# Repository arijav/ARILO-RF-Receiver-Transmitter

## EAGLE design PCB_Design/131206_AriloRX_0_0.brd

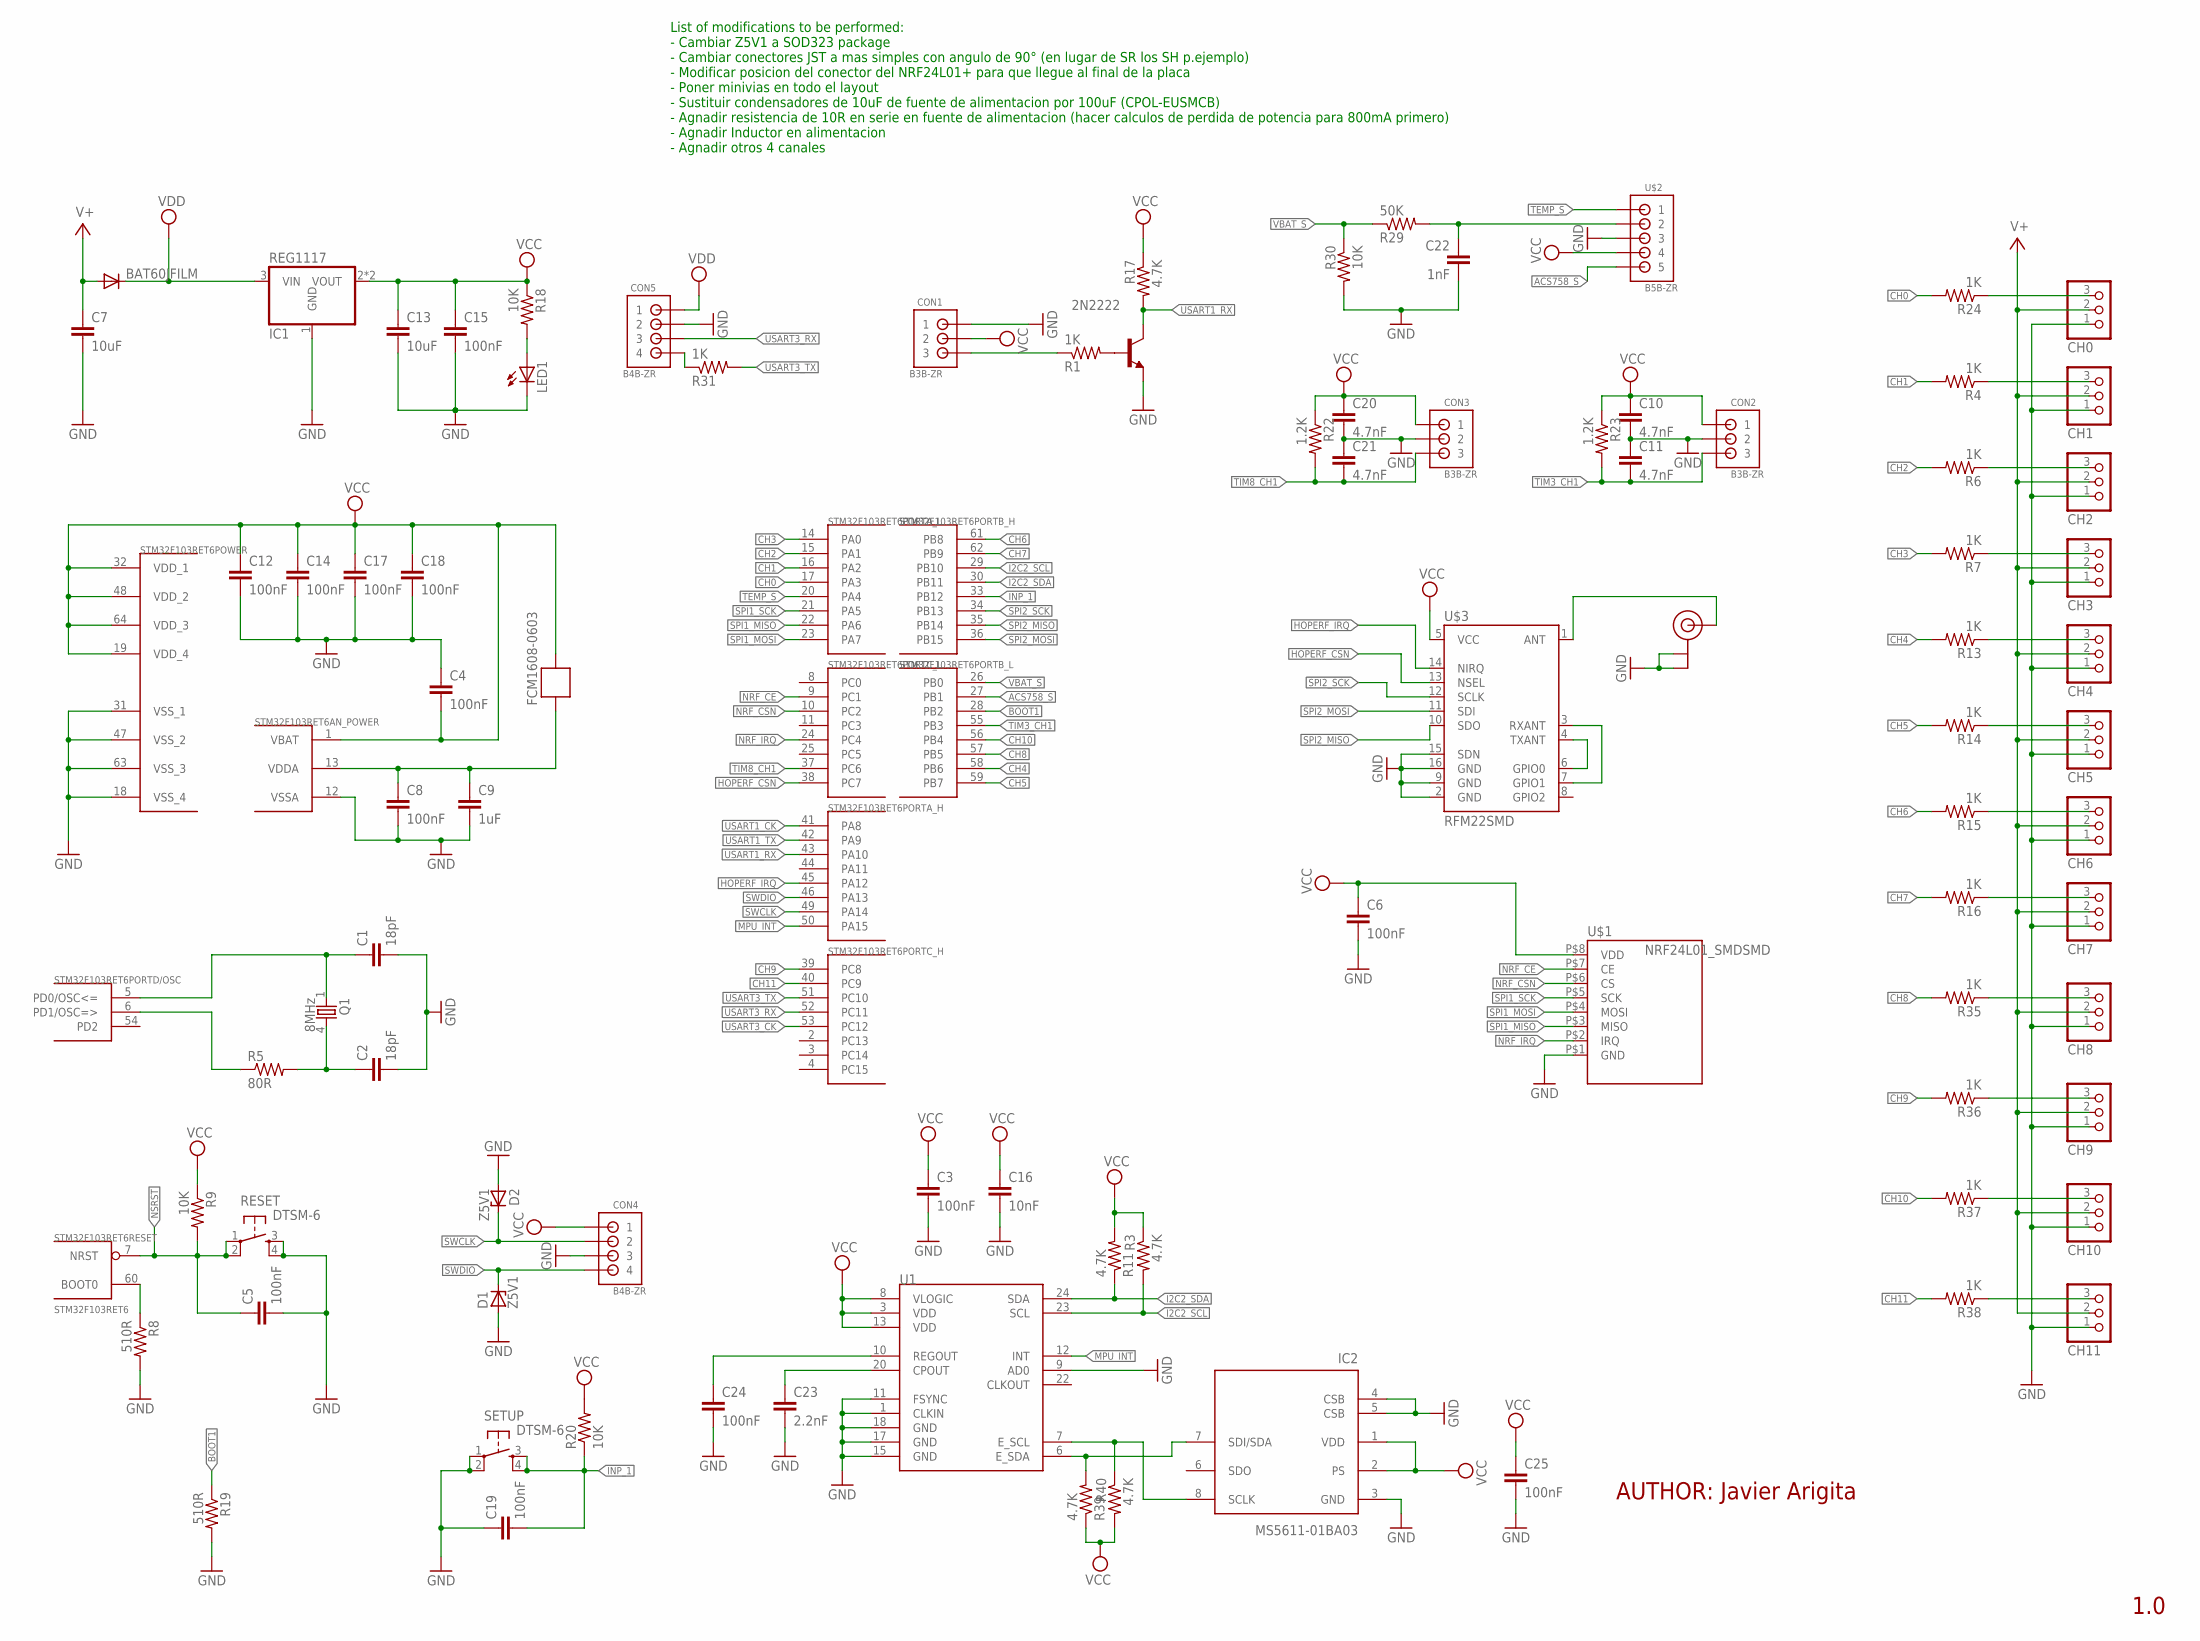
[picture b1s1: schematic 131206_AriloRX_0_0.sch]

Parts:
2N2222: MMBT2222ALT1-NPN-SOT23-BEC; SOT23-BEC
BAT60JFILM: DIODE-SOD323-R; SOD323-R
C1, C2: 18pF; C0805
C3, C4, C5, C6, C8, C12, C14, C15, C17, C18, C19, C24, C25: 100nF; C0805
C7, C13: 10uF; C3216
C9: 1uF; C3216
C10, C11, C20, C21: 4.7nF; C0805
C16: 10nF; C0805
C22: 1nF; C0805
C23: 2.2nF; C0805
CH0, CH1, CH2, CH3, CH4, CH5, CH6, CH7, CH8, CH9, CH10, CH11: PINHD-1X3; 1X03
CON1, CON2, CON3: B3B-ZR
CON4, CON5: B4B-ZR
D1, D2: Z5V1; SOD80C
FCM1608-0603: FERRITE-BEAD; R0603
IC1: REG1117; SOT223
IC2: MS5611-01BA03; SON125P300X500X100-8N
LED1: LED0805; CHIPLED_0805
Q1: 8MHz; MA506
R1, R4, R6, R7, R13, R14, R15, R16, R24, R31, R35, R36, R37, R38: 1K; R0805
R3, R11, R17, R39, R40: 4.7K; R0805
R5: 80R; R0805
R8, R19: 510R; R0805
R9, R18, R20, R30: 10K; R0805
R22, R23: 1.2K; R0805
R29: 50K; R0805
RESET: DTSM-6
SETUP: DTSM-6
STM32F103RET6: STM32F103RET6; TQFP64
U1: MPU-9150QFN-24-NP; QFN-24-NP
U$1: NRF24L01_SMDSMD; NRF24L01_SMD
U$2: B5B-ZR
U$3: RFM22SMD; RFM22-XXX-S2
U$4: U.FL

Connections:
ACS758_S: STM32F103RET6.27 (PB1), U$2.5
BOOT1: R19.1, STM32F103RET6.28 (PB2)
CH0: R24.2, STM32F103RET6.17 (PA3)
CH1: R4.2, STM32F103RET6.16 (PA2)
CH2: R6.2, STM32F103RET6.15 (PA1)
CH3: R7.2, STM32F103RET6.14 (PA0)
CH4: R13.2, STM32F103RET6.58 (PB6)
CH5: R14.2, STM32F103RET6.59 (PB7)
CH6: R15.2, STM32F103RET6.61 (PB8)
CH7: R16.2, STM32F103RET6.62 (PB9)
CH8: R35.2, STM32F103RET6.57 (PB5)
CH9: R36.2, STM32F103RET6.39 (PC8)
CH10: R37.2, STM32F103RET6.56 (PB4)
CH11: R38.2, STM32F103RET6.40 (PC9)
GND: 2N2222.E, C1.2, C2.2, C3.2, C4.1, C5.2, C6.2, C7.2, C8.2, C9.2, C10.2, C11.1, C12.2, C13.2, C14.2, C15.2, C16.2, C17.2, C18.2, C19.1, C20.2, C21.1, C22.2, C23.2, C24.2, C25.2, CH0.1, CH1.1, CH2.1, CH3.1, CH4.1, CH5.1, CH6.1, CH7.1, CH8.1, CH9.1, CH10.1, CH11.1, CON1.1, CON2.2, CON3.2, CON4.3, CON5.2, D1.A, D2.A, IC1.1 (GND), IC2.3 (GND), IC2.4 (CSB), IC2.5 (CSB), LED1.C, R8.2, R19.2, R30.2, RESET.3, RESET.4, SETUP.1, SETUP.2, STM32F103RET6.12 (VSSA), STM32F103RET6.18 (VSS_4), STM32F103RET6.31 (VSS_1), STM32F103RET6.47 (VSS_2), STM32F103RET6.63 (VSS_3), U1.1 (CLKIN), U1.9 (AD0), U1.11 (FSYNC), U1.15 (GND), U1.17 (GND), U1.18 (GND), U$1.P$1 (GND), U$2.3, U$3.2 (GND), U$3.9 (GND), U$3.15 (SDN), U$3.16 (GND), U$4.P$1 (GND), U$4.P$2 (GND)
HOPERF_CSN: STM32F103RET6.38 (PC7), U$3.13 (NSEL)
HOPERF_IRQ: STM32F103RET6.45 (PA12), U$3.14 (NIRQ)
I2C2_SCL: R3.2, STM32F103RET6.29 (PB10), U1.23 (SCL)
I2C2_SDA: R11.1, STM32F103RET6.30 (PB11), U1.24 (SDA)
INP_1: C19.2, R20.1, SETUP.3, SETUP.4, STM32F103RET6.33 (PB12)
MPU_INT: STM32F103RET6.50 (PA15), U1.12 (INT)
unnamed: C1.1, Q1.1, STM32F103RET6.5 (PD0/OSC<=)
unnamed: R5.1, STM32F103RET6.6 (PD1/OSC=>)
unnamed: C2.1, Q1.4 (2), R5.2
unnamed: R8.1, STM32F103RET6.60 (BOOT0)
unnamed: U$3.3 (RXANT), U$3.7 (GPIO1)
unnamed: U$3.4 (TXANT), U$3.6 (GPIO0)
unnamed: U$3.1 (ANT), U$4.P$3 (SIGNAL)
unnamed: CH0.3, R24.1
unnamed: LED1.A, R18.2
unnamed: CON5.4, R31.1
unnamed: CH8.3, R35.1
unnamed: CON1.3, R1.1
unnamed: C22.1, R29.2, U$2.2
unnamed: 2N2222.B, R1.2
unnamed: C8.1, C9.1, FCM1608-0603.2, STM32F103RET6.13 (VDDA)
unnamed: CH2.3, R6.1
unnamed: CH4.3, R13.1
unnamed: CH9.3, R36.1
unnamed: CH10.3, R37.1
unnamed: CH11.3, R38.1
unnamed: IC2.8 (SCLK), R40.1, U1.7 (E_SCL)
unnamed: IC2.7 (SDI/SDA), R39.2, U1.6 (E_SDA)
unnamed: CH3.3, R7.1
unnamed: CH6.3, R15.1
unnamed: C23.1, U1.20 (CPOUT)
unnamed: CH5.3, R14.1
unnamed: CH7.3, R16.1
unnamed: C24.1, U1.10 (REGOUT)
unnamed: CH1.3, R4.1
NRF_CE: STM32F103RET6.9 (PC1), U$1.P$7 (CE)
NRF_CSN: STM32F103RET6.10 (PC2), U$1.P$6 (CS)
NRF_IRQ: STM32F103RET6.24 (PC4), U$1.P$2 (IRQ)
NSRST: C5.1, R9.2, RESET.1, RESET.2, STM32F103RET6.7 (NRST)
SPI1_MISO: STM32F103RET6.22 (PA6), U$1.P$3 (MISO)
SPI1_MOSI: STM32F103RET6.23 (PA7), U$1.P$4 (MOSI)
SPI1_SCK: STM32F103RET6.21 (PA5), U$1.P$5 (SCK)
SPI2_MISO: STM32F103RET6.35 (PB14), U$3.10 (SDO)
SPI2_MOSI: STM32F103RET6.36 (PB15), U$3.11 (SDI)
SPI2_SCK: STM32F103RET6.34 (PB13), U$3.12 (SCLK)
SWCLK: CON4.2, D2.C, STM32F103RET6.49 (PA14)
SWDIO: CON4.4, D1.C, STM32F103RET6.46 (PA13)
TEMP_S: STM32F103RET6.20 (PA4), U$2.1
TIM3_CH1: C11.2, CON2.3, R23.2, STM32F103RET6.55 (PB3)
TIM8_CH1: C21.2, CON3.3, R22.2, STM32F103RET6.37 (PC6)
USART1_CK: STM32F103RET6.41 (PA8)
USART1_RX: 2N2222.C, R17.2, STM32F103RET6.43 (PA10)
USART1_TX: STM32F103RET6.42 (PA9)
USART3_CK: STM32F103RET6.53 (PC12)
USART3_RX: CON5.3, STM32F103RET6.52 (PC11)
USART3_TX: R31.2, STM32F103RET6.51 (PC10)
V+: BAT60JFILM.A, C7.1, CH0.2, CH1.2, CH2.2, CH3.2, CH4.2, CH5.2, CH6.2, CH7.2, CH8.2, CH9.2, CH10.2, CH11.2
VBAT_S: R29.1, R30.1, STM32F103RET6.26 (PB0)
VCC: C3.1, C4.2, C6.1, C10.1, C12.1, C13.1, C14.1, C15.1, C16.1, C17.1, C18.1, C20.1, C25.1, CON1.2, CON2.1, CON3.1, CON4.1, FCM1608-0603.1, IC1.2 (VOUT), IC1.4 (VOUT), IC2.1 (VDD), IC2.2 (PS), R3.1, R9.1, R11.2, R17.1, R18.1, R20.2, R22.1, R23.1, R39.1, R40.2, STM32F103RET6.1 (VBAT), STM32F103RET6.19 (VDD_4), STM32F103RET6.32 (VDD_1), STM32F103RET6.48 (VDD_2), STM32F103RET6.64 (VDD_3), U1.3 (VDD), U1.8 (VLOGIC), U1.13 (VDD), U$1.P$8 (VDD), U$2.4, U$3.5 (VCC)
VDD: BAT60JFILM.C, CON5.1, IC1.3 (VIN)

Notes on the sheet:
AUTHOR: Javier Arigita
1.0
List of modifications to be performed: - Cambiar Z5V1 a SOD323 package - Cambiar conectores JST a mas simples con angulo de 90° (en lugar de SR los SH p.ejemplo) - Modificar posicion del conector del NRF24L01+ para que llegue al final de la placa - Poner minivias en todo el layout - Sustituir conde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

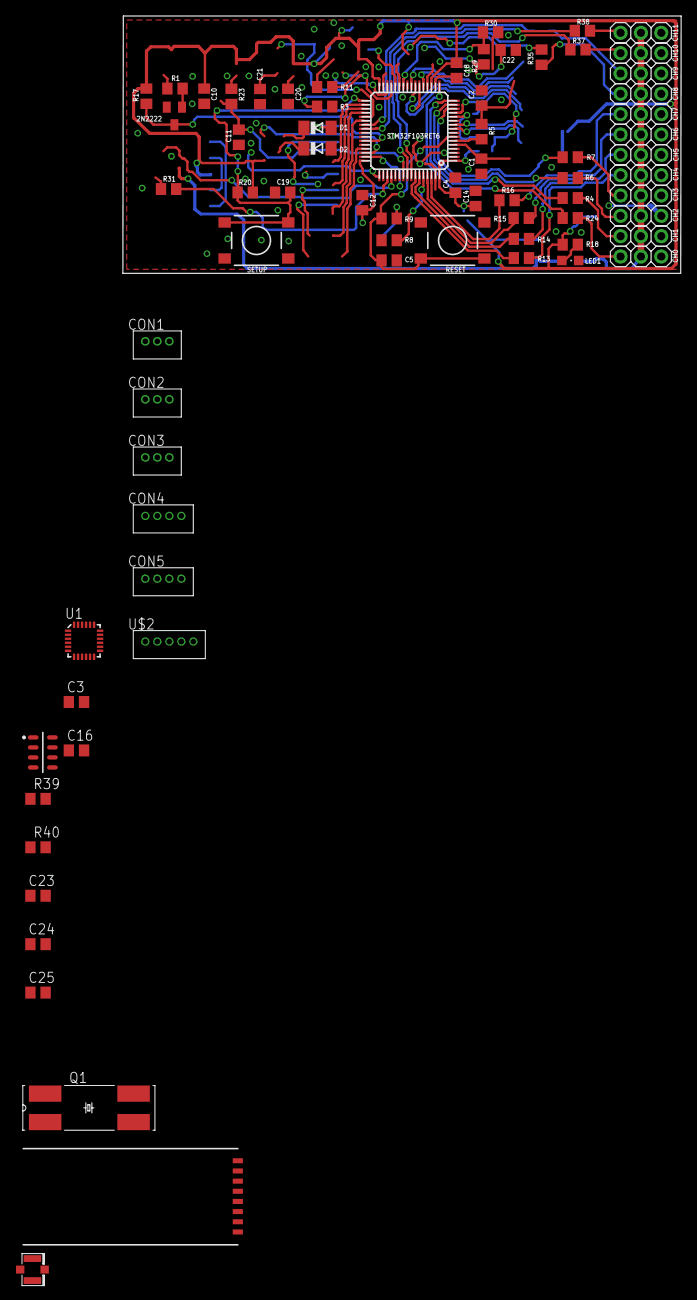
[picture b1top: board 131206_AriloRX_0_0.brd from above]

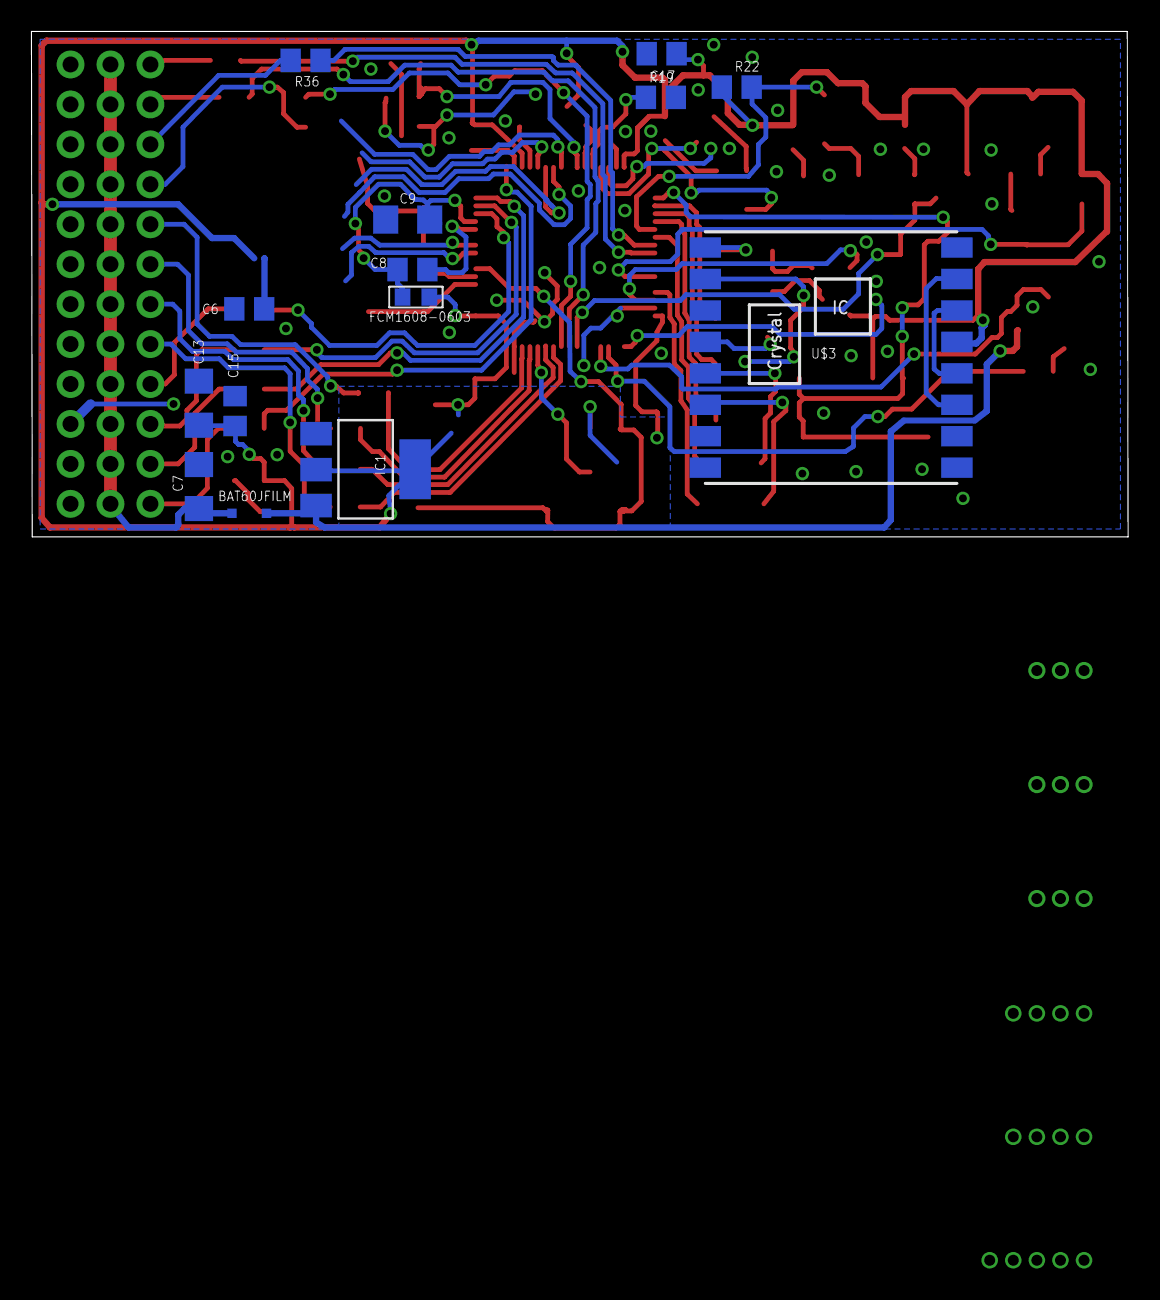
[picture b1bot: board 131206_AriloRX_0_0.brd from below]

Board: 2 copper layers, 69.7 x 32.1 mm, 88 parts (14 on the bottom side), 72 nets.

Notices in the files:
parts and their libraries:
SparkFun-RF: Licensing: CC v3.0 Share-Alike You are welcome to use this library for commercial purposes.
